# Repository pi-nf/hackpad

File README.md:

# DavinciPad
My macropad for Davinci Resolve! Made for Hackclub's Highway/Hackpad event.

## Screenshots
Thank you guide - these were done in KiCad. For the first time I think it wasn't bad?

Skirk silkscreen!! Art by [きつみ](https://www.pixiv.net/en/users/5786297)!

For the case I wanted to show off the PCB so I've made just a base to prop it up!

## BOM
| Component                                 | Quantity |
|-------------------------------------------|----------|
| 2L PCB (JLCPCB!!)                         | 1        |
| Seeed Studio XIAO RP2040                  | 1        |
| Gateron Milky Yellows Cherry MX Switches  | 6        |
| 1N4148 Diodes (THT)                       | 6        |
| M3 Screws                                 | 3        |
| M3 Heat inserts                           | 3        |
| All from the hackpad kit with the exception of the PCB!! Totals to | **$3.49** |

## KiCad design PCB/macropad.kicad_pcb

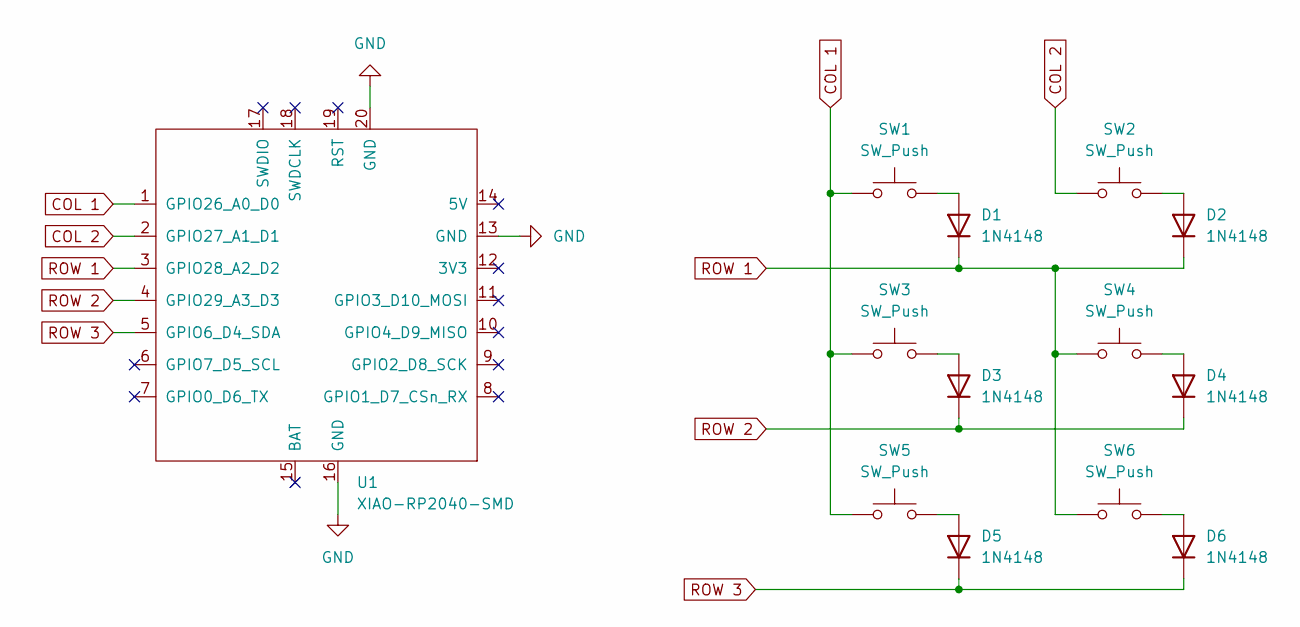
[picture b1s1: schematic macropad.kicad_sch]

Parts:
D1, D2, D3, D4, D5, D6: 1N4148; D_DO-35_SOD27_P7.62mm_Horizontal
SW1, SW2, SW3, SW4, SW5, SW6: SW_Push; SW_Cherry_MX_1.00u_PCB
U1: XIAO-RP2040-SMD; XIAO_rp2040_SMD

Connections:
COL 1: SW1.1, SW3.1, SW5.1, U1.1 (GPIO26_A0_D0)
COL 2: SW2.1, U1.2 (GPIO27_A1_D1)
GND: U1.13 (GND), U1.16 (GND), U1.20 (GND)
unnamed: D1.2 (A), SW1.2
unnamed: D2.2 (A), SW2.2
unnamed: D3.2 (A), SW3.2
unnamed: D4.2 (A), SW4.2
unnamed: D5.2 (A), SW5.2
unnamed: D6.2 (A), SW6.2
ROW 1: D1.1 (K), D2.1 (K), SW4.1, SW6.1, U1.3 (GPIO28_A2_D2)
ROW 2: D3.1 (K), D4.1 (K), U1.4 (GPIO29_A3_D3)
ROW 3: D5.1 (K), D6.1 (K), U1.5 (GPIO6_D4_SDA)

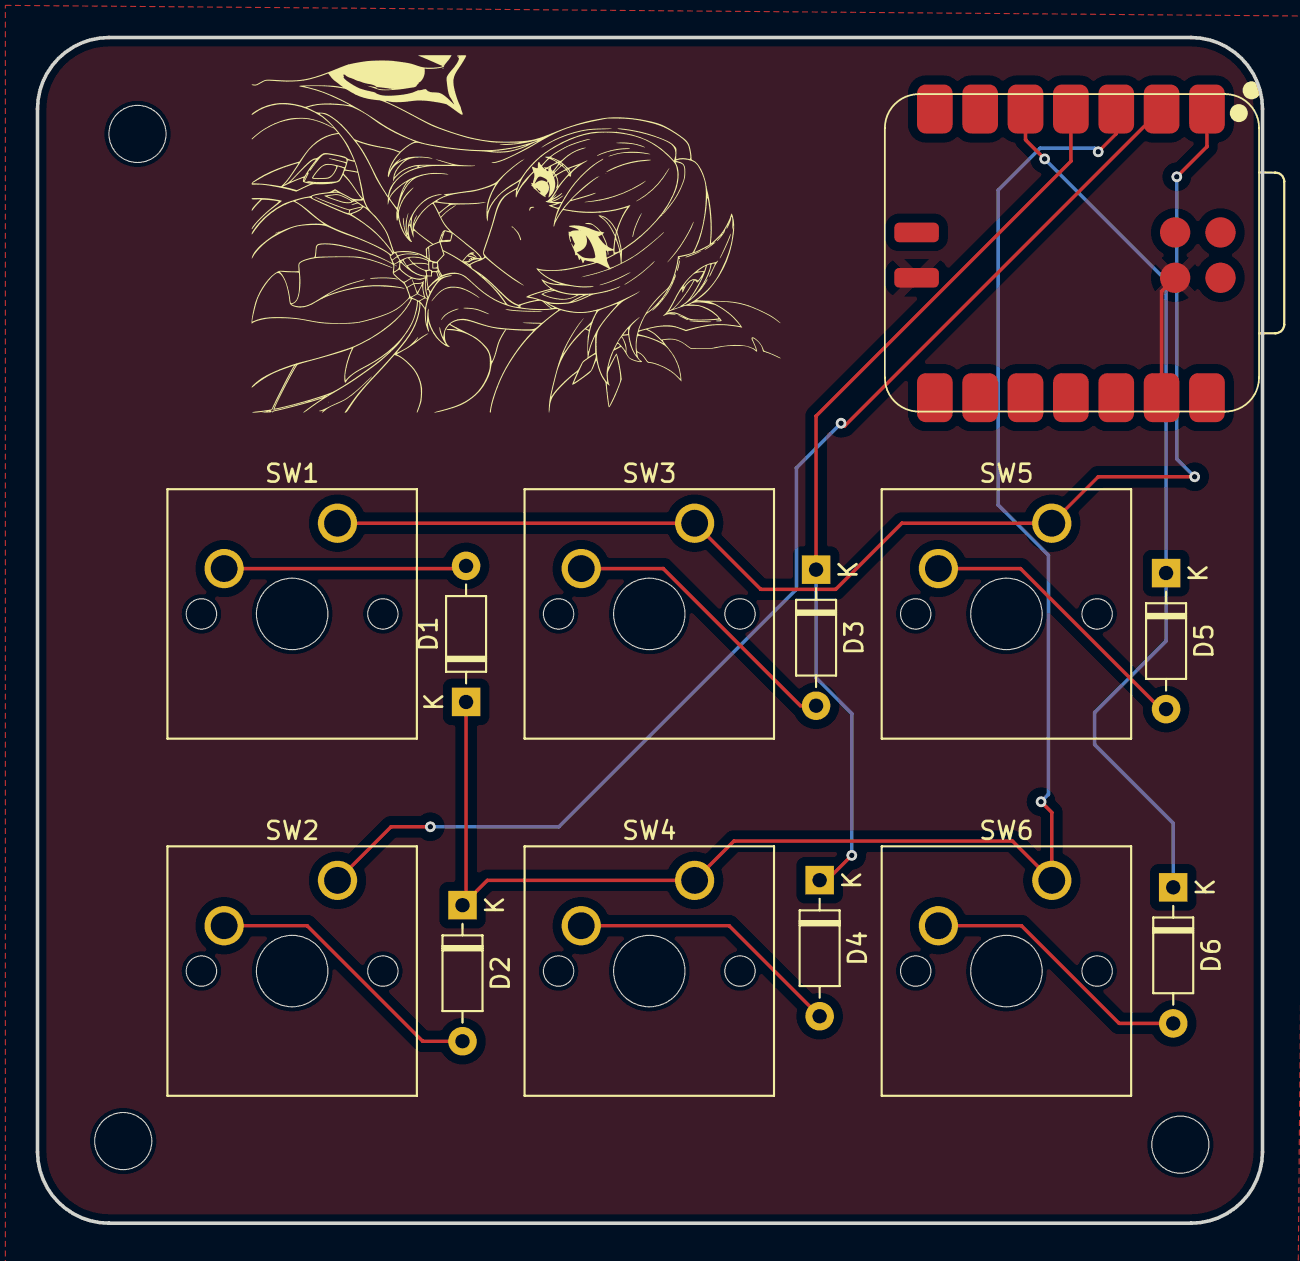
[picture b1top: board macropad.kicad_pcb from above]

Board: 2 copper layers, 68.6 x 66.4 mm, 13 parts (0 on the bottom side), 12 nets.

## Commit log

2025-07-05 Upload Macropad!
2025-07-06 Upload .stl to /production
2025-07-07 Upload Case .stl again
2025-07-07 Upload Case .3mf
